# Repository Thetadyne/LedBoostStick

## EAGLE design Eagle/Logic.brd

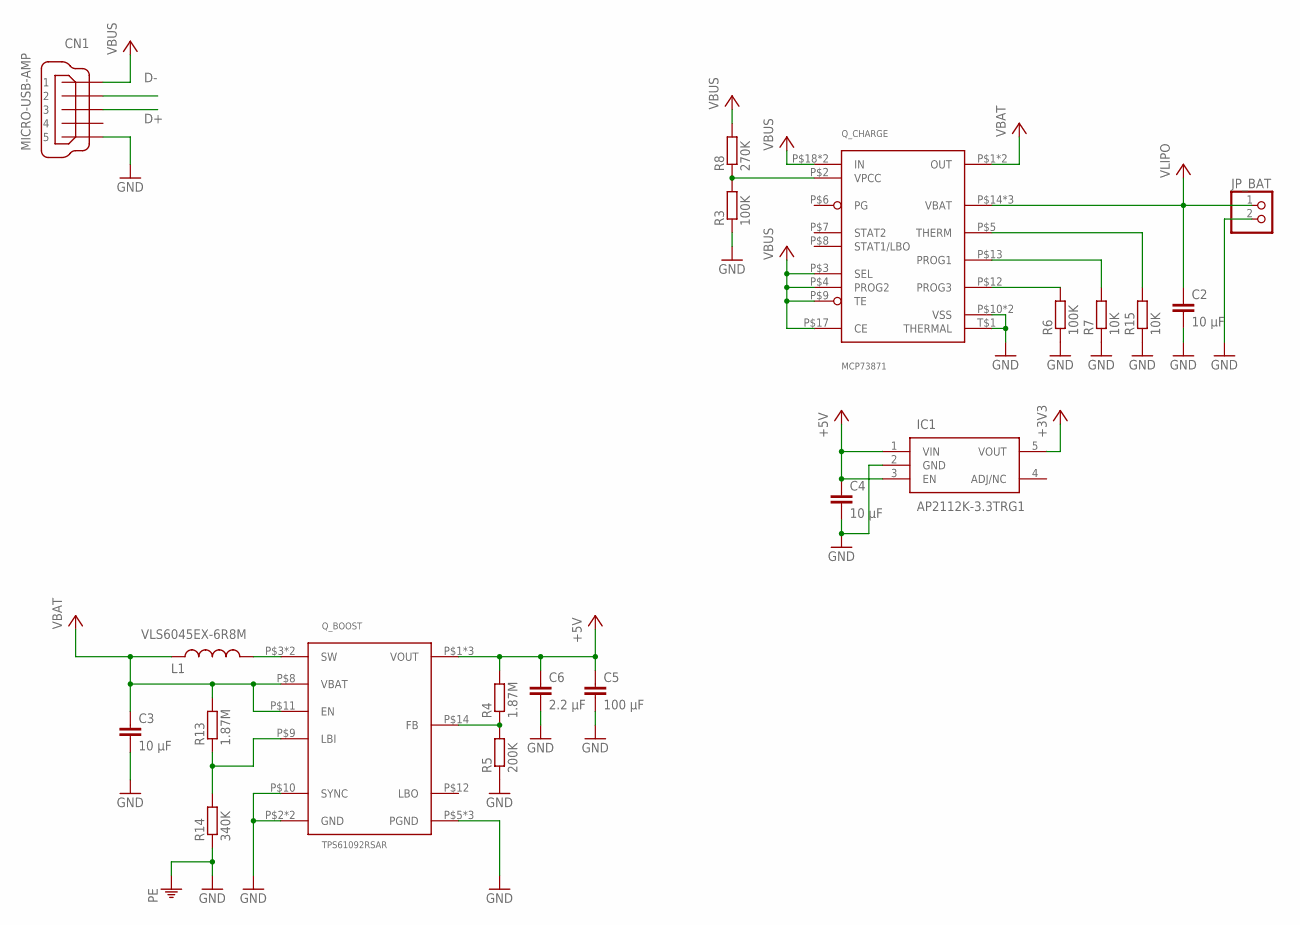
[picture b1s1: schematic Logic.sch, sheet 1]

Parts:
C2, C3, C4: 10 μF; C0603
C5: 100 μF; C1206
C6: 2.2 μF; C0603
CN1: MICRO-USB-AMP; 10118193-0001LF
IC1: AP2112K-3.3TRG1; SOT95P282X130-5N
JP_BAT: PINHD-1X2; 1X02
L1: VLS6045EX-6R8M
Q_BOOST: TPS61092RSAR
Q_CHARGE: MCP73871
R3, R6: 100K; R0603
R4, R13: 1.87M; R0603
R5: 200K; R0603
R7, R15: 10K; R0603
R8: 270K; R0603
R14: 340K; R0603

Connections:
+3V3: IC1.5 (VOUT); also elsewhere on the board
+5V: C4.1, C5.1, C6.1, IC1.1 (VIN), IC1.3 (EN), Q_BOOST.P$1 (VOUT), Q_BOOST.P$15 (VOUT), Q_BOOST.P$16 (VOUT), R4.2; also elsewhere on the board
D+: CN1.3; also elsewhere on the board
D-: CN1.2; also elsewhere on the board
FB: Q_BOOST.P$14 (FB), R4.1, R5.2
GND: C2.2, C3.2, C4.2, C5.2, C6.2, CN1.5, CN1.G1 (5), CN1.G2 (5), IC1.2 (GND), JP_BAT.2, Q_BOOST.P$2 (GND), Q_BOOST.P$5 (PGND), Q_BOOST.P$6 (PGND), Q_BOOST.P$7 (PGND), Q_BOOST.P$10 (SYNC), Q_BOOST.P$13 (GND), Q_CHARGE.P$10 (VSS), Q_CHARGE.P$11 (VSS), Q_CHARGE.T$1 (THERMAL), R3.1, R5.1, R6.1, R7.1, R14.1, R15.1; also elsewhere on the board
unnamed: Q_BOOST.P$9 (LBI), R13.1, R14.2
unnamed: Q_CHARGE.P$12 (PROG3), R6.2
unnamed: Q_CHARGE.P$13 (PROG1), R7.2
unnamed: Q_CHARGE.P$5 (THERM), R15.2
SW: L1.P$2 (2), Q_BOOST.P$3 (SW), Q_BOOST.P$4 (SW)
VBAT: C3.1, L1.P$1 (1), Q_BOOST.P$8 (VBAT), Q_BOOST.P$11 (EN), Q_CHARGE.P$1 (OUT), Q_CHARGE.P$20 (OUT), R13.2
VBUS: CN1.1, Q_CHARGE.P$3 (SEL), Q_CHARGE.P$4 (PROG2), Q_CHARGE.P$9 (TE), Q_CHARGE.P$17 (CE), Q_CHARGE.P$18 (IN), Q_CHARGE.P$19 (IN), R8.2
VLIPO: C2.1, JP_BAT.1, Q_CHARGE.P$14 (VBAT), Q_CHARGE.P$15 (VBAT), Q_CHARGE.P$16 (VBAT); also elsewhere on the board
VPCC: Q_CHARGE.P$2 (VPCC), R3.2, R8.1

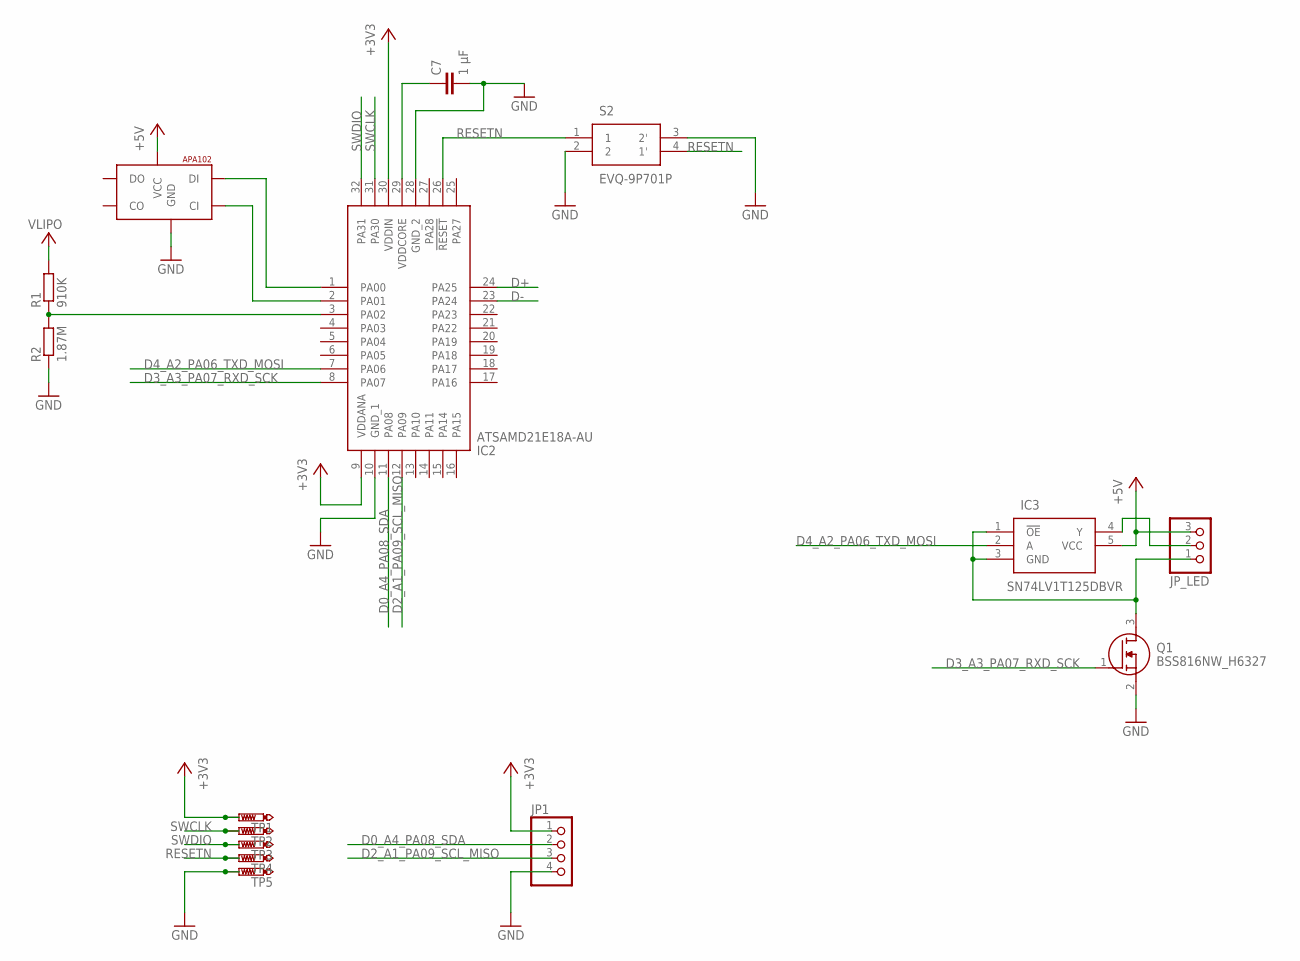
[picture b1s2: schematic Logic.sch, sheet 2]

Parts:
C7: 1 μF; C0603
IC2: ATSAMD21E18A-AU; QFP80P900X900X120-32N
IC3: SN74LV1T125DBVR; SOT95P280X145-5N
JP1: PINHD-1X4; 1X04
JP_LED: PINHD-1X3; 1X03
Q1: BSS816NW_H6327; SOT65P210X100-3N
R1: 910K; R0603
R2: 1.87M; R0603
S2: EVQ-9P701P
TP1, TP2, TP3, TP4, TP5: PTR1B2,54; B2,54
U$2: APA1025050; APA102_5050

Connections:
+3V3: IC2.9 (VDDANA), IC2.30 (VDDIN), JP1.1, TP1.TP; also elsewhere on the board
+5V: IC3.5 (VCC), JP_LED.3, U$2.1 (VCC); also elsewhere on the board
D0_A4_PA08_SDA: IC2.11 (PA08), JP1.2
D2_A1_PA09_SCL_MISO: IC2.12 (PA09), JP1.3
D3_A3_PA07_RXD_SCK: IC2.8 (PA07), Q1.1 (G)
D4_A2_PA06_TXD_MOSI: IC2.7 (PA06), IC3.2 (A)
D+: IC2.24 (PA25); also elsewhere on the board
D-: IC2.23 (PA24); also elsewhere on the board
GND: C7.2, IC2.10 (GND_1), IC2.28 (GND_2), JP1.4, Q1.2 (S), R2.1, S2.2, S2.3 (2'), TP5.TP, U$2.6 (GND); also elsewhere on the board
unnamed: IC2.3 (PA02), R1.1, R2.2
unnamed: IC2.2 (PA01), U$2.5 (CI)
unnamed: IC3.1 (!OE), IC3.3 (GND), JP_LED.1, Q1.3 (D)
unnamed: IC3.4 (Y), JP_LED.2
unnamed: IC2.1 (PA00), U$2.4 (DI)
unnamed: C7.1, IC2.29 (VDDCORE)
RESETN: IC2.26 (!RESET), S2.1, S2.4 (1'), TP4.TP
SWCLK: IC2.31 (PA30), TP2.TP
SWDIO: IC2.32 (PA31), TP3.TP
VLIPO: R1.2; also elsewhere on the board

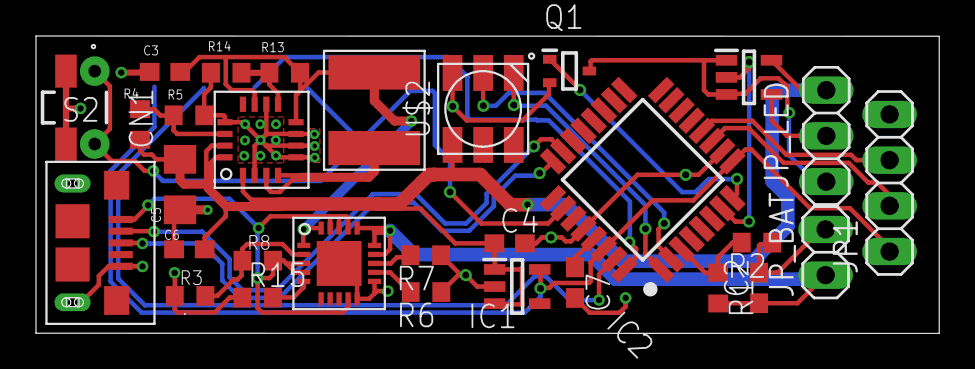
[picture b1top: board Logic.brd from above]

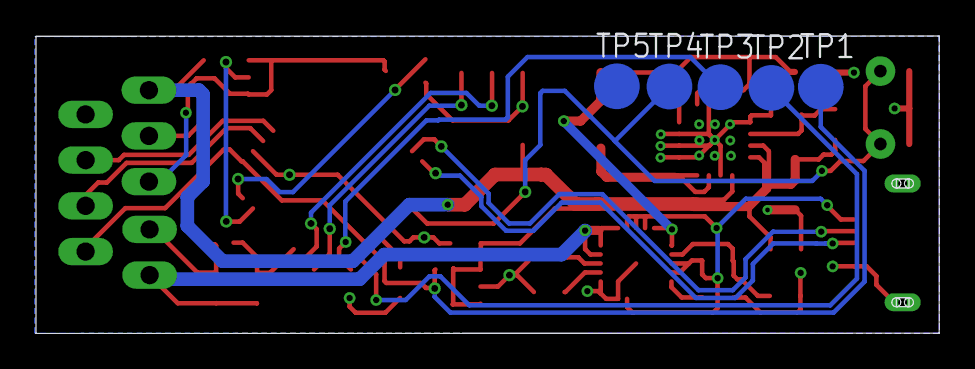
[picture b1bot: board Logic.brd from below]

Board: 2 copper layers, 50.2 x 16.5 mm, 35 parts (5 on the bottom side), 28 nets.

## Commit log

2019-12-11 Init Pop
